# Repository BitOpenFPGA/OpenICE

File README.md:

OpeniCE
-----------

# 来源 

开源FPGA应具备几个维度特点：

其中最难弄得就是工具链了，经过长时间查找，终于在GitHub上找到了一个FPGA的开源工具链Yosys，选择的理由如下：

Intel Quartus II （No ）License

Xilinx Vivado ISE (No) License

Lattice Diamond (No) License 注册可以免费申请，但是随时可以收回（一般不会）

 Yosys, nextpnr, icestorm, iverilog, symbiflow （YES） 整个工具链开源

支持的硬件：

http://www.clifford.at/icestorm/

折中选择ICE40UP5K-SG48芯片。

为什么选择ICE40系列FPGA呢？

Lattice的iCE40系列芯片在国外很受欢迎，大部分的开发环境都是开源的，不需要担心License所带来的限制，只需要将工具链进行安装之后就可以进行FPGA的开发之路，典型的基于iCE40系列的开源开发板有iCEBreaker、UPduino、BlackIce、iCEstick、TinyFPGA 等。

每个开发版对比如下：
表格来源：https://www.crowdsupply.com/1bitsquared/icebreaker-fpga

|                                         | iCEBreaker                       | TinyFPGA BX        | Tomu FPGA          | Lattice ICEstick              | UPDuino v2.0                  | ICE40UP5K Breakout            | Alhambra II                  | ICE40HX8K Breakout            |
| :-------------------------------------- | :------------------------------- | :----------------- | :----------------- | :---------------------------- | :---------------------------- | :---------------------------- | :--------------------------- | :---------------------------- |
| License                                 | OSHW                             | OSHW               | OSHW               | Closed                        | Closed                        | Closed                        | OSHW                         | Closed                        |
| Price                                   | $65                              | $38                | $??                | ~$25                          | $13.99                        | $49                           | $59.90                       | $49                           |
| Schematics Published?                   | Yes                              | Yes                | Not Yet            | Yes                           | Yes                           | Yes                           | Yes                          | Yes                           |
| Design files Published?                 | Yes                              | Yes                | Not Yet            | No                            | Yes                           | No                            | Yes                          | No                            |
| **FPGA**                                |                                  |                    |                    |                               |                               |                               |                              |                               |
| Model                                   | iCE40UP5K                        | iCE40LP8K          | iCE40UP5K          | iCE40HX1K                     | iCE40UP5K                     | iCE40UP5K                     | iCE40HX4K(8K)                | iCE40HX8K                     |
| Logic Capacity (LUTs)                   | 5280                             | 7680               | 5280               | 1280                          | 5280                          | 5280                          | 3520 (7680)                  | 7680                          |
| Internal RAM (bits)                     | 120k + 1024k                     | 128k               | 120k + 1024k       | 64k                           | 120k + 1024k                  | 120k + 1024k                  | 80k                          | 128k                          |
| Multipliers                             | 8                                | 0                  | 8                  | 0                             | 8                             | 8                             | 0                            | 0                             |
| **Peripherals**                         |                                  |                    |                    |                               |                               |                               |                              |                               |
| USB Interface                           | FTDI 2232HQ                      | On FPGA Bootloader | On FPGA Bootloader | FTDI 2232HL                   | FTDI 232HQ                    | FTDI 2232HL                   | FTDI 2232HQ                  | FTDI 2232HL                   |
| USB HS FIFO/SPI interface to the FPGA   | Yes through Jumper Mod           | No                 | No                 | No                            | No                            | No                            | No                           | No                            |
| USB Serial (UART) interface to the FPGA | Yes                              | No                 | No                 | Yes                           | No                            | Yes                           | Yes                          | Yes                           |
| GPIO inline termination resistors       | Yes 33 Ohm                       | No                 | No                 | No                            | No                            | No                            | Yes 300 Ohm                  | No                            |
| User IOs                                | 27 + 7                           | 41 + 2             | 4 + 2              | 18                            | 34                            | 34 + 2                        | 20                           | 90 + 10                       |
| Pmod Connectors                         | 3                                | 0                  | 0                  | 1                             | 0                             | 1                             | 0                            | 0                             |
| User Buttons                            | 1 Tact + 3 Tact on Breakoff Pmod | 1 CRESET           | 2 Capacitive       | 0                             | 0                             | 4 DIP                         | 2 Tact                       | 0                             |
| User LED                                | 2 + 5 on Breakoff Pmod           | 1                  | 0                  | 5                             | 1 RGB                         | 1 RGB                         | 8                            | 8                             |
| Indicator LED                           | PWR, CDONE                       | PWR                |                    |                               | CDONE, FTDI-TX/RX             | PWR, CDONE                    | PWR, CDONE, FTDI-TX/RX       | PWR, CDONE                    |
| Onboard Clock                           | 12 MHz MEMS Shared with FTDI     | 16 MHz MEMS        | 12 MHz MEMS        | 12 MHz MEMS? Shared with FTDI | 12 MHz MEMS? Shared with FTDI | 12 MHz MEMS? Shared with FTDI | 12 MHz MEMS Shared with FTDI | 12 MHz MEMS? Shared with FTDI |
| Flash                                   | 128 Mbit QSPI DDR                | 8 Mbit SPI         | 16 Mbit SPI        | 32 Mbit SPI                   | 32 Mbit SPI                   | 32 Mbit SPI                   | 32 Mbit SPI                  | 32 Mbit SPI                   |
| **FPGA Power Delivery**                 |                                  |                    |                    |                               |                               |                               |                              |                               |
| Dedicated GND/Power Planes              | Yes                              | Yes                | No                 | Yes                           | No                            | Yes                           | Yes                          | Yes                           |
| Dedicated FPGA Bypass Capacitors        | 19                               | 8                  | 9                  | 18                            | 2                             | 19                            | ?                            | ?                             |
| IO GND Connections                      | 11                               | 6                  | 1                  | 4                             | 3                             | 8                             | 22                           | 20                            |
| **Software**                            |                                  |                    |                    |                               |                               |                               |                              |                               |
| Open Source Toolchain                   | Yes                              | Yes                | Yes                | Yes                           | Yes                           | Yes                           | Yes                          | Yes                           |
| APIO                                    | Yes                              | Yes                | Yes                | Yes                           | Yes                           | Yes                           | Yes                          | Yes                           |
| icestudio                               | Yes                              | Yes                | Not Yet            | Yes                           | Yes                           | Yes                           | Yes                          | Yes                           |
| migen                                   | Yes                              | Yes                | No                 | Yes                           | No                            | Yes                           | No                           | Yes                           |

硬件上也可以参考：https://github.com/icebreaker-fpga/icebreaker-examples

其中icebreaker可以直接采购，但是国内买还是偏难，而且价格上也比较贵，综合考虑还是自己参考官方的DEMO和icebreaker自己做，原则上尽量减少改动。

# OpenICE介绍 
OpenICE 是基于Lattice iCE40UP5k设计的开源FPGA开发板，开发板以Arduino为原型进行设计，资源丰富，板载RGB LED，KEY，TYPE-C-USB, RESET，大部分IO以标准PMOD接口引出，可与标准PMOD外设进行对接，方便日常的开发使用。  
板载的调试器以FT2232H为核心设计，支持官方的EDA进行下载调试，同时经过开源工具链ICEProg就可实现轻松实现烧写。FT2232H同时支持虚拟串口和FPGA进行通信。  

整版的原理框图如下：

PCB截图如下：

# 芯片规格 
iCE40UP5K-SG48  
1. 5280 Logic Cells (4-LUT + Carry + FF)  
2. 128 KBit Dual-Port Block RAM  
3. 1 MBit (128 KB) Single-Port RAM  
4. PLL, Two SPI and two I2C hard IPs  
5. Two internal oscillators (10 kHz and 48 MHz)  
6. 8 DSPs (16x16 multiply + 32 bit accumulate)  
7. 3x 24mA drive and 3x hard PWM IP  

# 硬件说明
### iCE40UP5K
1. SPI Flash使用W25Q64（8MB）/W25Q128(16MB)
2. 板载按键开关、LED和RGB LED可用于测试
3. 所有IO以标准PMOD接口引出
4. 板载电源指示灯V8，方便查看整版电源情况

**Capable enough to host CPU softcores**

- [picorv32](https://github.com/cliffordwolf/picorv32/)
- [picosoc](https://github.com/cliffordwolf/picorv32/tree/master/picosoc)
- [RISC-V](https://riscv.org/) and others

# 开发环境搭建
推荐使用虚拟机镜像进行开发测试，简单方便。  
FPGA工具链安装请参考[icestorm](http://www.clifford.at/icestorm/)  
gcc工具链安装请参考 [riscv-gnu-toolchain](https://pingu98.wordpress.com/2019/04/08/how-to-build-your-own-cpu-from-scratch-inside-an-fpga/)  

# FPGA教程

# 参考
### toolchain
http://www.clifford.at/icestorm/
### examples
https://github.com/damdoy/ice40_ultraplus_examples  
https://github.com/icebreaker-fpga/icebreaker-examples

### SpinalHDL 教程
https://spinalhdl.github.io/SpinalDoc-RTD/SpinalHDL/Getting%20Started/index.html
### 开源FPGA单板OpenICE介绍
https://github.com/OpenFPGA-ICE/OpenICE/blob/master/README.md

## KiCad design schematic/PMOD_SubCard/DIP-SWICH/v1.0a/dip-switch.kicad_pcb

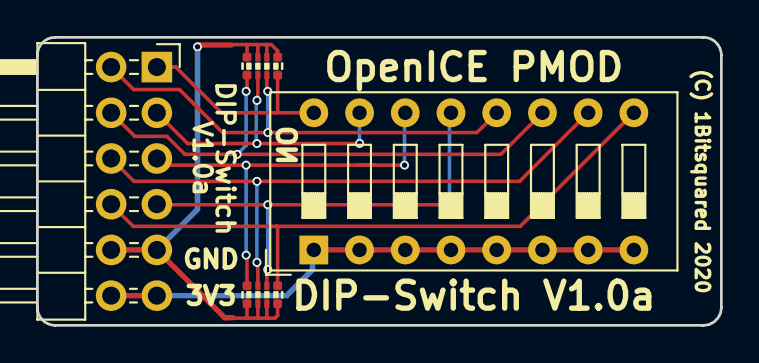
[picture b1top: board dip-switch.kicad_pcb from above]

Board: 2 copper layers, 38.0 x 16.0 mm, 4 parts (0 on the bottom side), 10 nets.

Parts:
J1: PMOD; PMODHeader_2x06_P2.54mm_Horizontal
R1, R2: 10k; R_Array_Convex_4x0402
SW1: SW_DIP_x08; SW_DIP_SPSTx08_Slide_9.78x22.5mm_W7.62mm_P2.54mm

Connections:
+3V3: J1.6, J1.12, SW1.1, SW1.2, SW1.3, SW1.4, SW1.5, SW1.6, SW1.7, SW1.8
/DIP1: J1.1, R1.2, SW1.16
/DIP2: J1.2, R1.6, SW1.15
/DIP3: J1.3, R2.2, SW1.14
/DIP4: J1.4, R2.6, SW1.13
/DIP5: J1.7, R1.4, SW1.12
/DIP6: J1.8, R1.8, SW1.11
/DIP7: J1.9, R2.4, SW1.10
/DIP8: J1.10, R2.8, SW1.9
GND: J1.5, J1.11, R1.1, R1.3, R1.5, R1.7, R2.1, R2.3, R2.5, R2.7

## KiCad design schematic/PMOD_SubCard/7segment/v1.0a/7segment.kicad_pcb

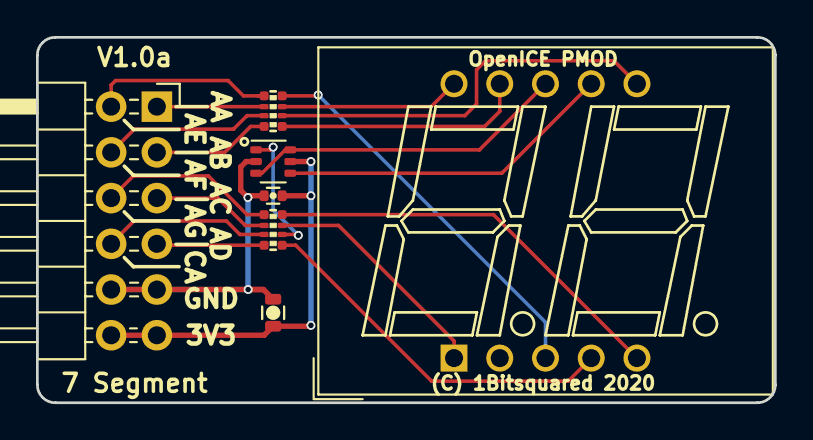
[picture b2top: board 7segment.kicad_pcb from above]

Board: 2 copper layers, 41.0 x 20.3 mm, 7 parts (0 on the bottom side), 20 nets.

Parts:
C1: 10u; C_0603
C2: 100n; C_0402
J1: PMOD; PMODHeader_2x06_P2.54mm_Horizontal
R1, R2: 330E; R_Array_Convex_4x0402
U1: SN450561N
U2: NL27WZ14; SOT-363_SC-70-6

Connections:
+3V3: C1.1, C2.1, J1.6, J1.12, U2.5
/AA: J1.1, R2.6
/AAx: R2.5, U1.10
/AB: J1.2, R2.2
/ABx: R2.1, U1.9
/AC: J1.3, R1.6
/ACx: R1.5, U1.1
/AD: J1.4, R1.2
/ADx: R1.1, U1.4
/AE: J1.7, R2.8
/AEx: R2.7, U1.3
/AF: J1.8, R2.4
/AFx: R2.3, U1.6
/AG: J1.9, R1.8
/AGx: R1.7, U1.5
/CAT: J1.10, R1.4
/CAT1: U1.8, U2.3, U2.6
/CAT2: U1.7, U2.4
/CATx: R1.3, U2.1
GND: C1.2, C2.2, J1.5, J1.11, U2.2

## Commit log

2020-07-22 second commit
2020-08-02 add 6502
2020-08-02 add picorv32
2020-08-02 add VexRiscv
2020-08-02 add icicle
2020-08-02 add litex-buildenv
2020-08-02 add iceZ0mble
2020-08-02 3rd commit
2020-08-08 4rd commit

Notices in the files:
schematic/PMOD_SubCard/7segment/v1.0a/7segment.kicad_pcb:
(C) 2019 Piotr Esden-Tempski
(C) 2019 1BitSquared
License: CC-BY-SA V4.0
CC-BY-SA
